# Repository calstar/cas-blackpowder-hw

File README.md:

View this project on [CADLAB.io](https://cadlab.io/project/23052). 

# cas-blackpowder-hw
Common Avionics Stack - Blackpowder Ignition Module - Hardware

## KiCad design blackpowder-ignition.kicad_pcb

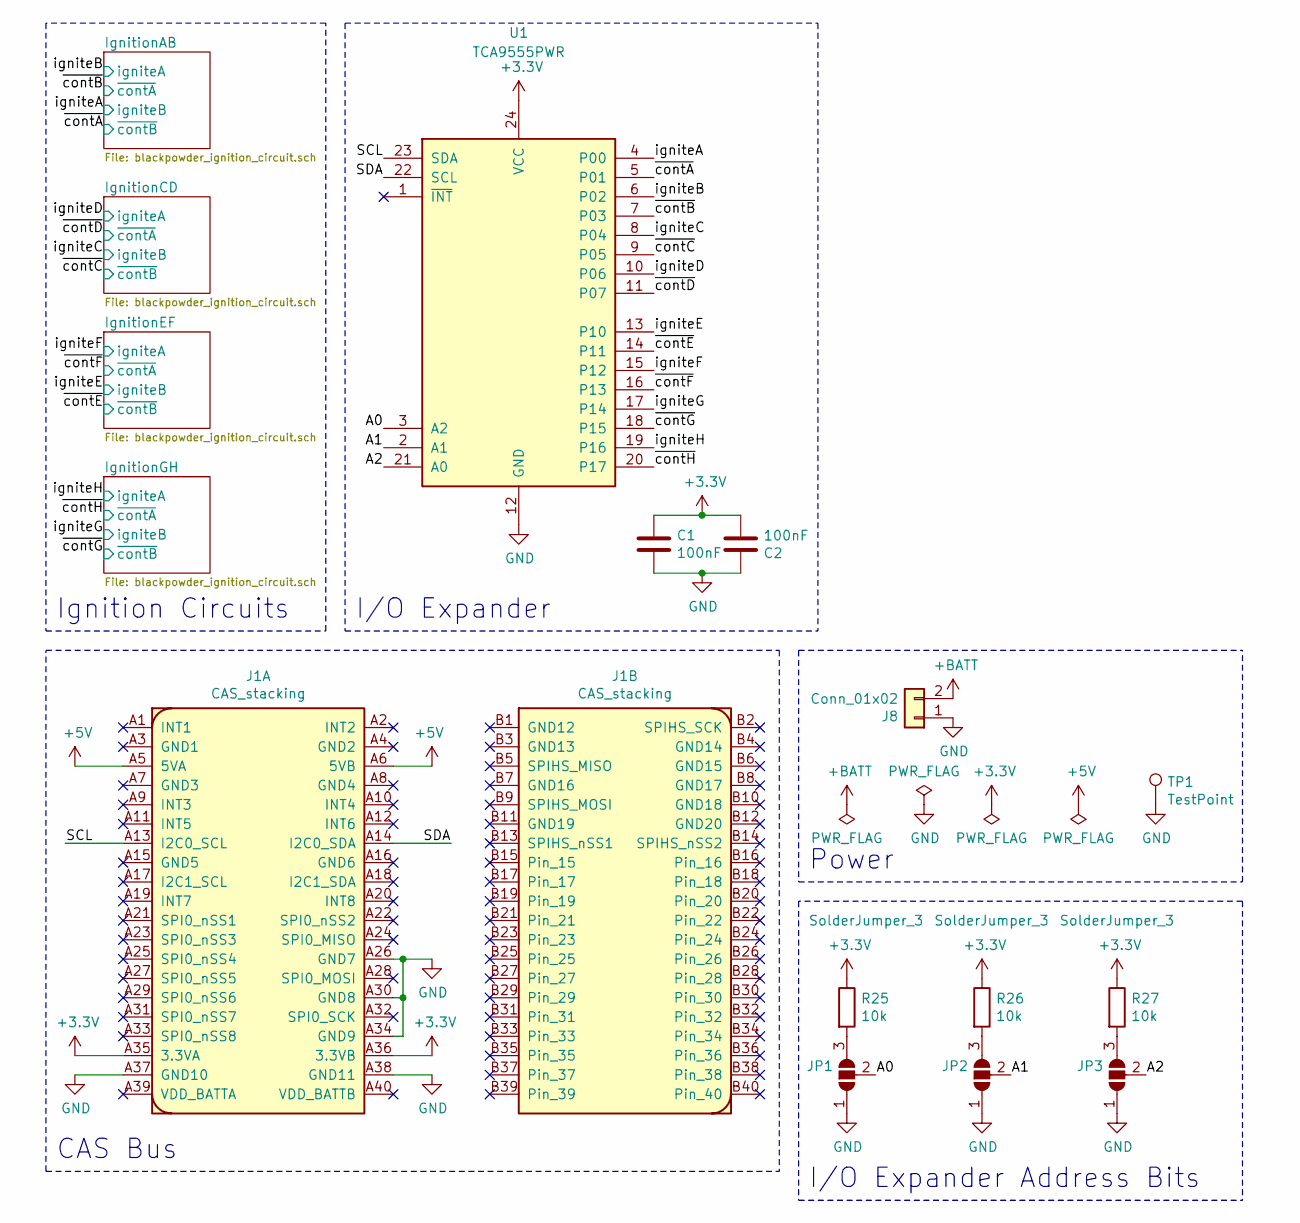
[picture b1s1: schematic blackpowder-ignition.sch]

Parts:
C1, C2: 100nF; C_0603_1608Metric_Pad1.08x0.95mm_HandSolder; DIGIKEY 399-1100-1-ND
J1: CAS_stacking; CAS_physical
J8: Conn_01x02; Molex_Mini-Fit_Jr_5569-02A2_2x01_P4.20mm_Horizontal; DIGIKEY WM16206-ND
JP1, JP2, JP3: SolderJumper_3; SolderJumper-3_P1.3mm_Open_RoundedPad1.0x1.5mm
R25, R26, R27: 10k; R_0603_1608Metric_Pad0.98x0.95mm_HandSolder; DIGIKEY 311-10KGRCT-ND
TP1: TestPoint; TestPoint_Keystone_5000-5004_Miniature
U1: TCA9555PWR; TSSOP-24_4.4x7.8mm_P0.65mm; DIGIKEY 296-24827-1-ND

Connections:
+3V3: C1.1, C2.2, J1.A35 (3.3VA), J1.A36 (3.3VB), R25.1, R26.1, R27.1, U1.24 (VCC); also elsewhere on the board
+5V: J1.A5 (5VA), J1.A6 (5VB); also elsewhere on the board
+BATT: J8.2; also elsewhere on the board
/A0: JP1.2 (C), U1.3 (A2)
/A1: JP2.2 (C), U1.2 (A1)
/A2: JP3.2 (C), U1.21 (A0)
/SCL: J1.A13 (I2C0_SCL), U1.23 (SDA)
/SDA: J1.A14 (I2C0_SDA), U1.22 (SCL)
/igniteA: U1.4 (P00); also elsewhere on the board
/igniteB: U1.6 (P02); also elsewhere on the board
/igniteC: U1.8 (P04); also elsewhere on the board
/igniteD: U1.10 (P06); also elsewhere on the board
/igniteE: U1.13 (P10); also elsewhere on the board
/igniteF: U1.15 (P12); also elsewhere on the board
/igniteG: U1.17 (P14); also elsewhere on the board
/igniteH: U1.19 (P16); also elsewhere on the board
/~contA~: U1.5 (P01); also elsewhere on the board
/~contB~: U1.7 (P03); also elsewhere on the board
/~contC~: U1.9 (P05); also elsewhere on the board
/~contD~: U1.11 (P07); also elsewhere on the board
/~contE~: U1.14 (P11); also elsewhere on the board
/~contF~: U1.16 (P13); also elsewhere on the board
/~contG~: U1.18 (P15); also elsewhere on the board
/~contH~: U1.20 (P17); also elsewhere on the board
GND: C1.2, C2.1, J1.A26 (GND7), J1.A30 (GND8), J1.A34 (GND9), J1.A37 (GND10), J1.A38 (GND11), J8.1, JP1.1 (A), JP2.1 (A), JP3.1 (A), TP1.1, U1.12 (GND); also elsewhere on the board
unnamed: JP1.3 (B), R25.2
unnamed: JP2.3 (B), R26.2
unnamed: JP3.3 (B), R27.2

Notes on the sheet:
I/O Expander
I/O Expander Address Bits
Ignition Circuits
Power
CAS Bus

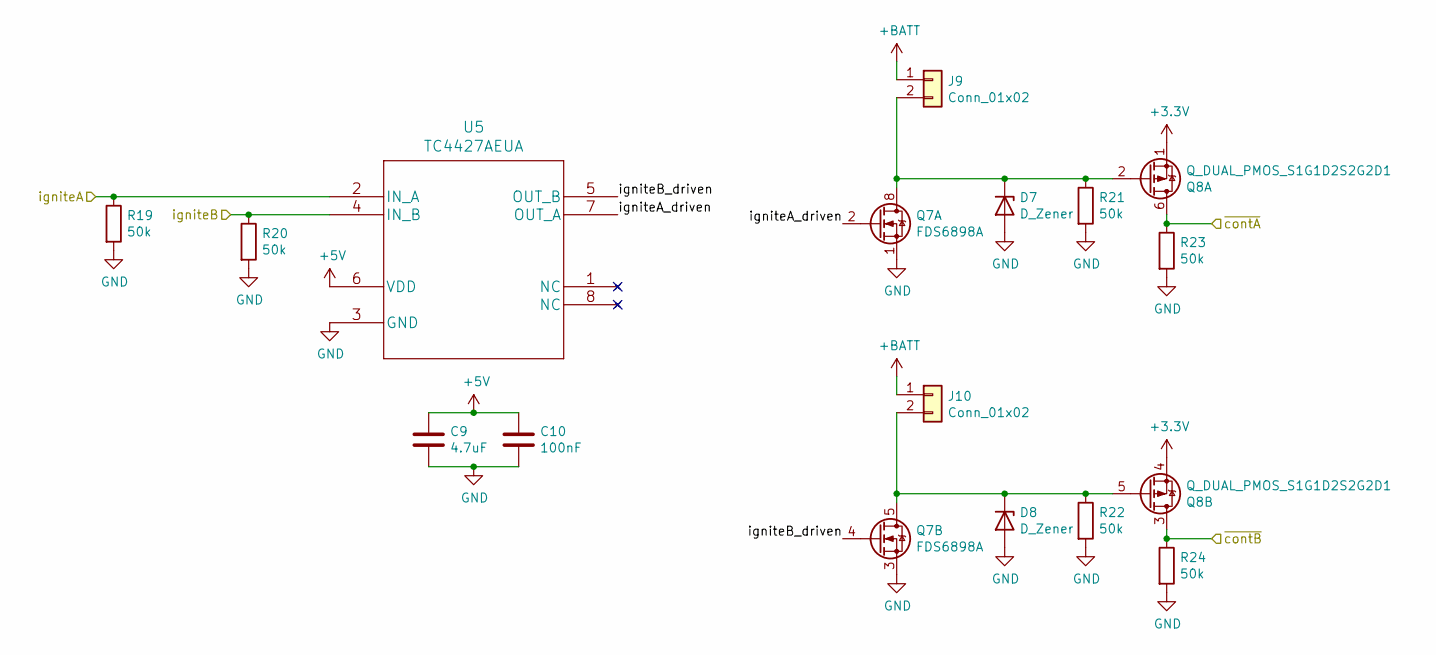
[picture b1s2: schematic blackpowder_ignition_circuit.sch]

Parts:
C5: 4.7uF; C_0603_1608Metric_Pad1.08x0.95mm_HandSolder; DIGIKEY 1276-1784-1-ND
C6: 100nF; C_0603_1608Metric_Pad1.08x0.95mm_HandSolder; DIGIKEY 399-1100-1-ND
D1, D2: D_Zener; D_0603_1608Metric_Pad1.05x0.95mm_HandSolder; DIGIKEY 497-16271-1-ND
J2, J3: Conn_01x02; Molex_Mini-Fit_Jr_5569-02A2_2x01_P4.20mm_Horizontal; DIGIKEY WM16206-ND
Q1: FDS6898A; SOIC-8_3.9x4.9mm_P1.27mm
Q2: Q_DUAL_PMOS_S1G1D2S2G2D1; SOT-363_SC-70-6_Handsoldering; DIGIKEY 742-SI1967DH-T1-BE3CT-ND
R1, R2, R3, R4, R5, R6: 50k; R_0603_1608Metric_Pad0.98x0.95mm_HandSolder; DIGIKEY 311-51KGRCT-ND
U2: TC4427AEUA; DIGIKEY TC4427AEUA-ND

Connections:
+3V3: Q2.1 (S), Q2.4 (S); also elsewhere on the board
+5V: C5.1, C6.1, U2.6 (VDD); also elsewhere on the board
+BATT: J2.1, J3.1; also elsewhere on the board
/IgnitionAB/igniteA_driven: Q1.2 (G1), U2.7 (OUT_A)
/IgnitionAB/igniteB_driven: Q1.4 (G2), U2.5 (OUT_B)
/igniteA: R2.1, U2.4 (IN_B); also elsewhere on the board
/igniteB: R1.1, U2.2 (IN_A); also elsewhere on the board
/~contA~: Q2.3 (D), R6.1; also elsewhere on the board
/~contB~: Q2.6 (D), R5.1; also elsewhere on the board
GND: C5.2, C6.2, D1.2 (A), D2.2 (A), Q1.1 (S1), Q1.3 (S2), R1.2, R2.2, R3.2, R4.2, R5.2, R6.2, U2.3 (GND); also elsewhere on the board
unnamed: D1.1 (K), J2.2, Q1.7 (D1), Q1.8 (D1), Q2.2 (G), R3.1
unnamed: D2.1 (K), J3.2, Q1.5 (D2), Q1.6 (D2), Q2.5 (G), R4.1

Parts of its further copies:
C3, C7, C9: 4.7uF; C_0603_1608Metric_Pad1.08x0.95mm_HandSolder; DIGIKEY 1276-1784-1-ND
C4, C8, C10: 100nF; C_0603_1608Metric_Pad1.08x0.95mm_HandSolder; DIGIKEY 399-1100-1-ND
D3, D4, D5, D6, D7, D8: D_Zener; D_0603_1608Metric_Pad1.05x0.95mm_HandSolder; DIGIKEY 497-16271-1-ND
J4, J5, J6, J7, J9, J10: Conn_01x02; Molex_Mini-Fit_Jr_5569-02A2_2x01_P4.20mm_Horizontal; DIGIKEY WM16206-ND
Q3, Q5, Q7: FDS6898A; SOIC-8_3.9x4.9mm_P1.27mm
R7, R8, R9, R10, R11, R12, R13, R14, R15, R16, R17, R18, R19, R20, R21, R22, R23, R24, R29: 50k; R_0603_1608Metric_Pad0.98x0.95mm_HandSolder; DIGIKEY 311-51KGRCT-ND

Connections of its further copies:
+5V: C3.1, C4.1, C7.1, C8.1, C9.1, C10.1; also elsewhere on the board
+BATT: J4.1, J5.1, J6.1, J7.1, J9.1, J10.1; also elsewhere on the board
/IgnitionCD/igniteA_driven: Q3.2 (G1); also elsewhere on the board
/IgnitionCD/igniteB_driven: Q3.4 (G2); also elsewhere on the board
/IgnitionEF/igniteA_driven: Q5.2 (G1); also elsewhere on the board
/IgnitionEF/igniteB_driven: Q5.4 (G2); also elsewhere on the board
/IgnitionGH/igniteA_driven: Q7.2 (G1); also elsewhere on the board
/IgnitionGH/igniteB_driven: Q7.4 (G2); also elsewhere on the board
/igniteC: R8.1; also elsewhere on the board
/igniteD: R7.1; also elsewhere on the board
/igniteE: R14.1; also elsewhere on the board
/igniteF: R13.1; also elsewhere on the board
/igniteG: R20.1; also elsewhere on the board
/igniteH: R19.1; also elsewhere on the board
/~contC~: R12.1; also elsewhere on the board
/~contD~: R11.1; also elsewhere on the board
/~contE~: R18.1; also elsewhere on the board
/~contF~: R17.1; also elsewhere on the board
/~contG~: R24.1; also elsewhere on the board
/~contH~: R23.1; also elsewhere on the board
GND: C3.2, C4.2, C7.2, C8.2, C9.2, C10.2, D3.2 (A), D4.2 (A), D5.2 (A), D6.2 (A), D7.2 (A), D8.2 (A), Q3.1 (S1), Q3.3 (S2), Q5.1 (S1), Q5.3 (S2), Q7.1 (S1), Q7.3 (S2), R7.2, R8.2, R9.2, R10.2, R11.2, R12.2, R13.2, R14.2, R15.2, R16.2, R17.2, R18.2, R19.2, R20.2, R21.2, R22.2, R23.2, R24.2; also elsewhere on the board
unnamed 35: D3.1 (K), J4.2, Q3.7 (D1), Q3.8 (D1), R9.1; also elsewhere on the board
unnamed 36: D4.1 (K), J5.2, Q3.5 (D2), Q3.6 (D2), R10.1; also elsewhere on the board
unnamed 37: D5.1 (K), J6.2, Q5.7 (D1), Q5.8 (D1), R15.1; also elsewhere on the board
unnamed 38: D6.1 (K), J7.2, Q5.5 (D2), Q5.6 (D2), R16.1; also elsewhere on the board
unnamed 39: D7.1 (K), J9.2, Q7.7 (D1), Q7.8 (D1), R21.1; also elsewhere on the board
unnamed 40: D8.1 (K), J10.2, Q7.5 (D2), Q7.6 (D2), R22.1; also elsewhere on the board

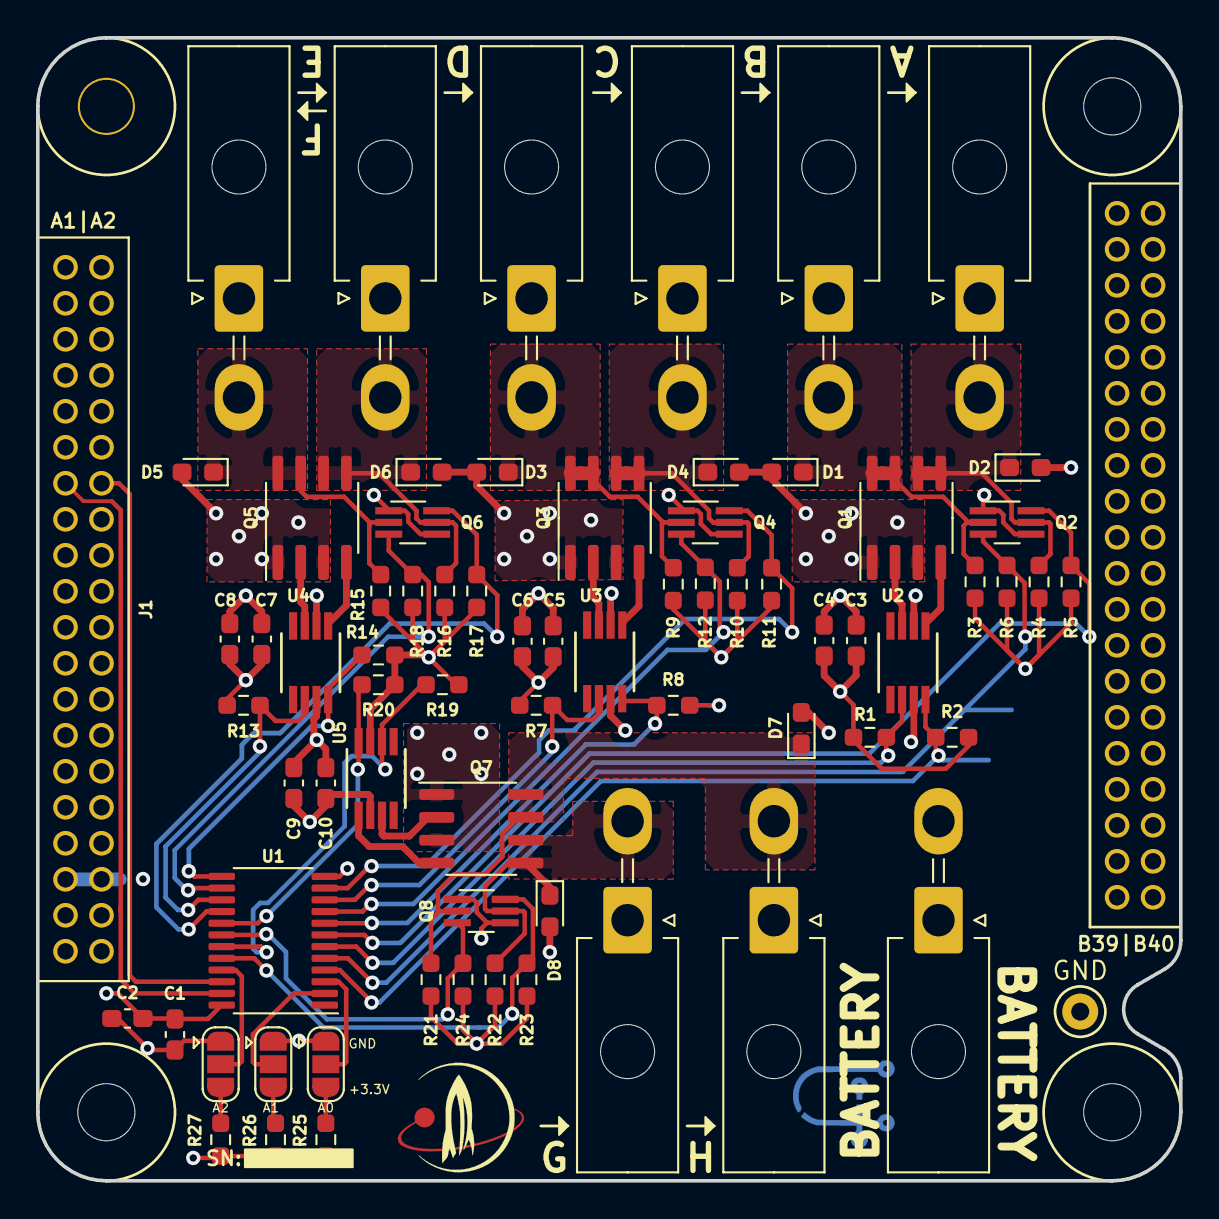
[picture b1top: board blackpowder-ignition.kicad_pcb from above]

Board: 4 copper layers, 63.5 x 63.5 mm, 74 parts (1 on the bottom side), 44 nets.

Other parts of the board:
Q4, Q6, Q8: Q_DUAL_PMOS_S1G1D2S2G2D1; SOT-363_SC-70-6_Handsoldering
Ref**: Val**; star_fancy
Ref**#2: Val**; bac
U3, U4, U5: MSOP8_MC_MCH; TC4427AEUA

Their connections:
+3V3: Q4.1, Q4.4, Q6.1, Q6.4, Q8.1, Q8.4; also elsewhere on the board
+5V: U3.6, U4.6, U5.6; also elsewhere on the board
/IgnitionCD/igniteA_driven: U3.7; also elsewhere on the board
/IgnitionCD/igniteB_driven: U3.5; also elsewhere on the board
/IgnitionEF/igniteA_driven: U4.7; also elsewhere on the board
/IgnitionEF/igniteB_driven: U4.5; also elsewhere on the board
/IgnitionGH/igniteA_driven: U5.7; also elsewhere on the board
/IgnitionGH/igniteB_driven: U5.5; also elsewhere on the board
/igniteC: U3.4; also elsewhere on the board
/igniteD: U3.2; also elsewhere on the board
/igniteE: U4.4; also elsewhere on the board
/igniteF: U4.2; also elsewhere on the board
/igniteG: U5.4; also elsewhere on the board
/igniteH: U5.2; also elsewhere on the board
/~contC~: Q4.3; also elsewhere on the board
/~contD~: Q4.6; also elsewhere on the board
/~contE~: Q6.3; also elsewhere on the board
/~contF~: Q6.6; also elsewhere on the board
/~contG~: Q8.3; also elsewhere on the board
/~contH~: Q8.6; also elsewhere on the board
GND: U3.3, U4.3, U5.3; also elsewhere on the board
unnamed 35: Q4.2; also elsewhere on the board
unnamed 36: Q4.5; also elsewhere on the board
unnamed 37: Q6.2; also elsewhere on the board
unnamed 38: Q6.5; also elsewhere on the board
unnamed 39: Q8.2; also elsewhere on the board
unnamed 40: Q8.5; also elsewhere on the board

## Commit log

2020-06-27 Backlink to CADLAB.io has been added.
2020-06-27 pushing blackpowder stuff to own repo
2020-06-28 removed circuits that can't be fit in
2020-06-28 updated submodules?
2020-06-29 everything hooked up, cleaned layout up, silkscreen
2020-07-04 pours for high current traces to connectors
2020-08-26 most functionality
2020-08-29 updated submodules to master
2020-12-30 8 charges on a module
2021-01-12 addressed review comments
2021-01-15 added digikey and manf part numbers, BAC logo
2021-01-26 updates based on review
2021-01-31 added diodes for esd
2021-04-10 using updated hardware sch blocks
